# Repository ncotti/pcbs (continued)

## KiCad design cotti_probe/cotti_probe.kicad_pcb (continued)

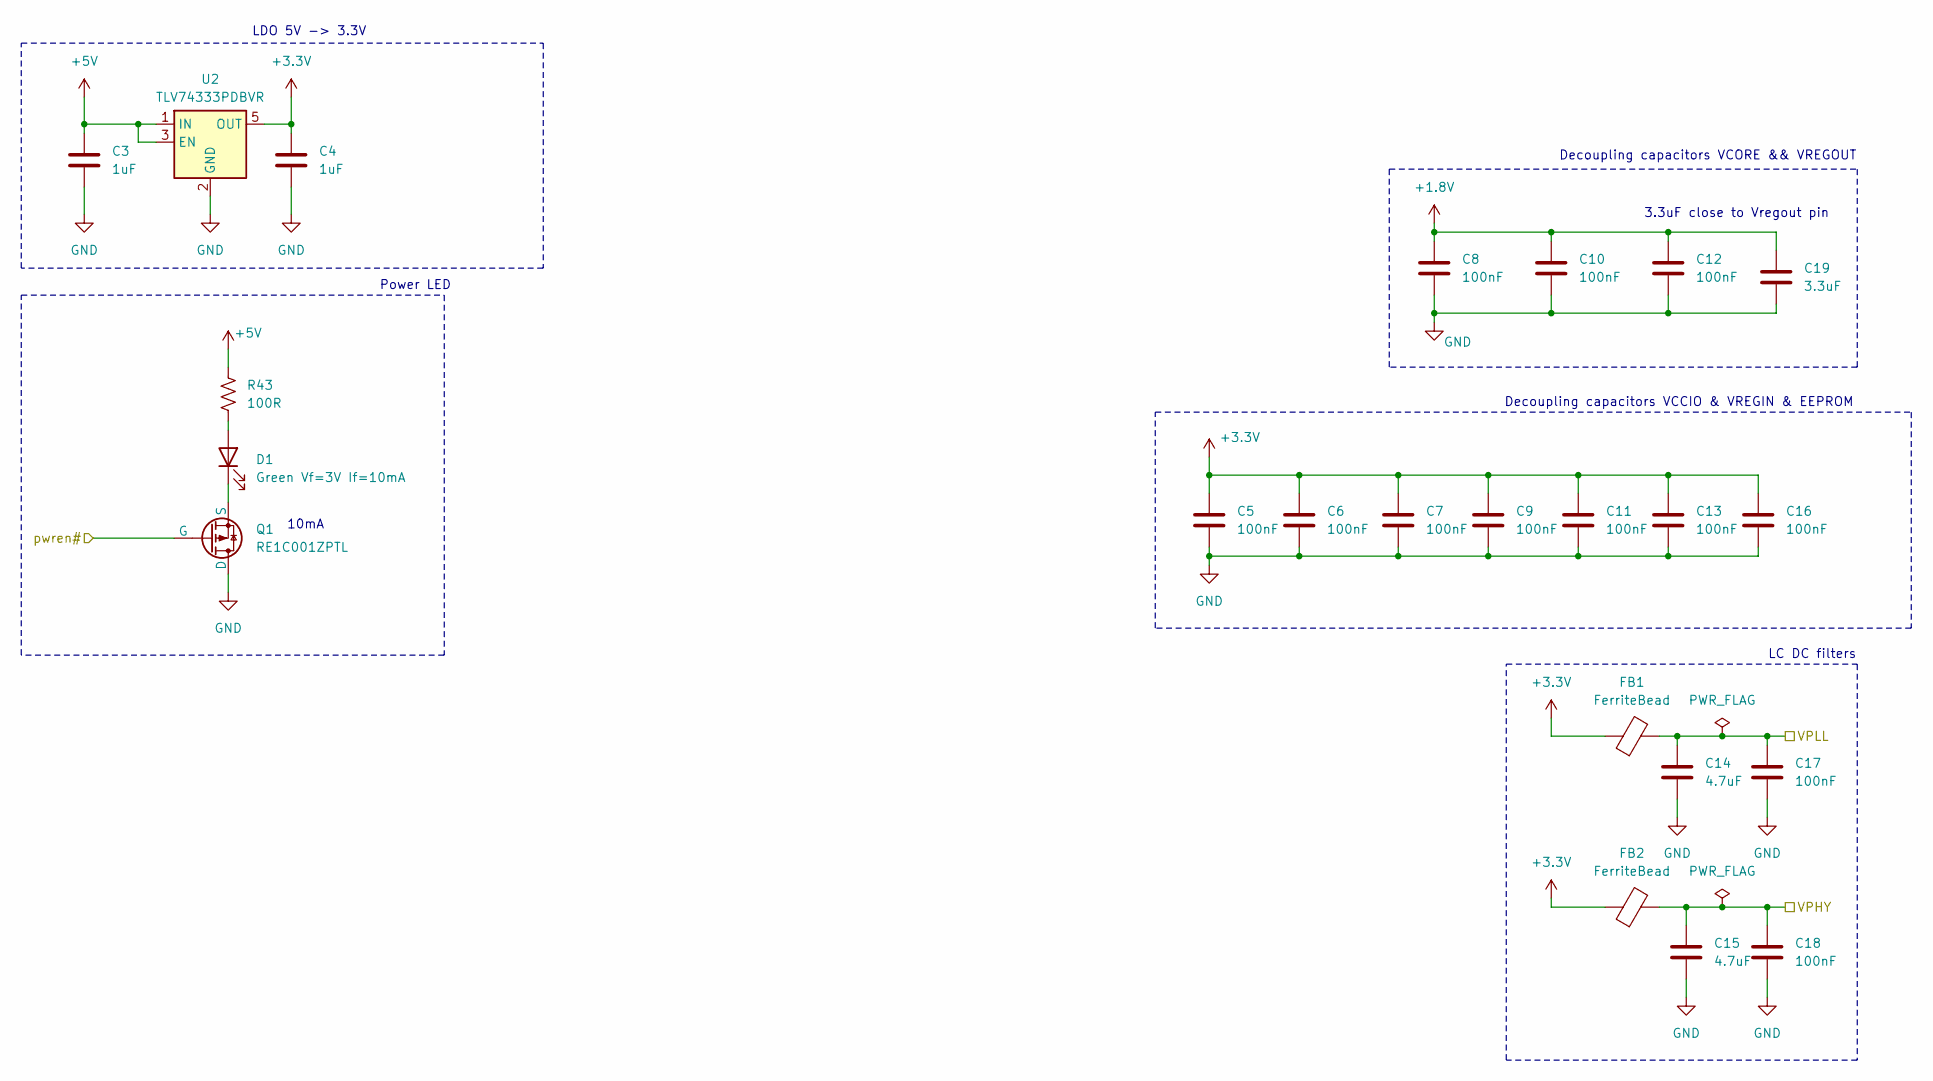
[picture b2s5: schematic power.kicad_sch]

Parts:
C3, C4: 1uF; C_0805_2012Metric_Pad1.18x1.45mm_HandSolder; Mfr. P/N CL21B105KBFNNNE
C5, C6, C7, C8, C9, C10, C11, C12, C13, C16, C17, C18: 100nF; C_0805_2012Metric_Pad1.18x1.45mm_HandSolder; Mfr. P/N CC0805KRX7R9BB104
C14, C15: 4.7uF; C_0805_2012Metric_Pad1.18x1.45mm_HandSolder; Mfr. P/N CL21A475KPFNNNE
C19: 3.3uF; C_0805_2012Metric_Pad1.18x1.45mm_HandSolder; Mfr. P/N CL21A335KPFNNNE
D1: Green Vf=3V If=10mA; LED_0603_1608Metric_Pad1.05x0.95mm_HandSolder; Mfr. P/N B1911PG--20D000514U1930
FB1, FB2: FerriteBead; L_0805_2012Metric_Pad1.05x1.20mm_HandSolder; Mfr. P/N MFBM1V2012-800-R
Q1: RE1C001ZPTL; SOT-416; Mfr. P/N RE1C001ZPTL
R43: 100R; R_0805_2012Metric_Pad1.20x1.40mm_HandSolder; Mfr. P/N RC0805FR-10100RL
U2: TLV74333PDBVR; SOT-23-5; Mfr. P/N TLV74333PDBVR

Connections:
+1.8V: C8.1, C10.1, C12.1, C19.1; also elsewhere on the board
+3.3V: C4.1, C5.1, C6.1, C7.1, C9.1, C11.1, C13.1, C16.1, FB1.1, FB2.1, U2.5 (OUT); also elsewhere on the board
+5V: C3.1, R43.1, U2.1 (IN), U2.3 (EN); also elsewhere on the board
/VPHY: C15.1, C18.1, FB2.2; also elsewhere on the board
/VPLL: C14.1, C17.1, FB1.2; also elsewhere on the board
/pwren#: Q1.1 (G); also elsewhere on the board
GND: C3.2, C4.2, C5.2, C6.2, C7.2, C8.2, C9.2, C10.2, C11.2, C12.2, C13.2, C14.2, C15.2, C16.2, C17.2, C18.2, C19.2, Q1.3 (D), U2.2 (GND); also elsewhere on the board
unnamed: D1.2 (A), R43.2
unnamed: D1.1 (K), Q1.2 (S)

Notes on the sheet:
Power LED
LC DC filters
10mA
LDO 5V -> 3.3V
3.3uF close to Vregout pin
Decoupling capacitors VCORE && VREGOUT
Decoupling capacitors VCCIO & VREGIN & EEPROM

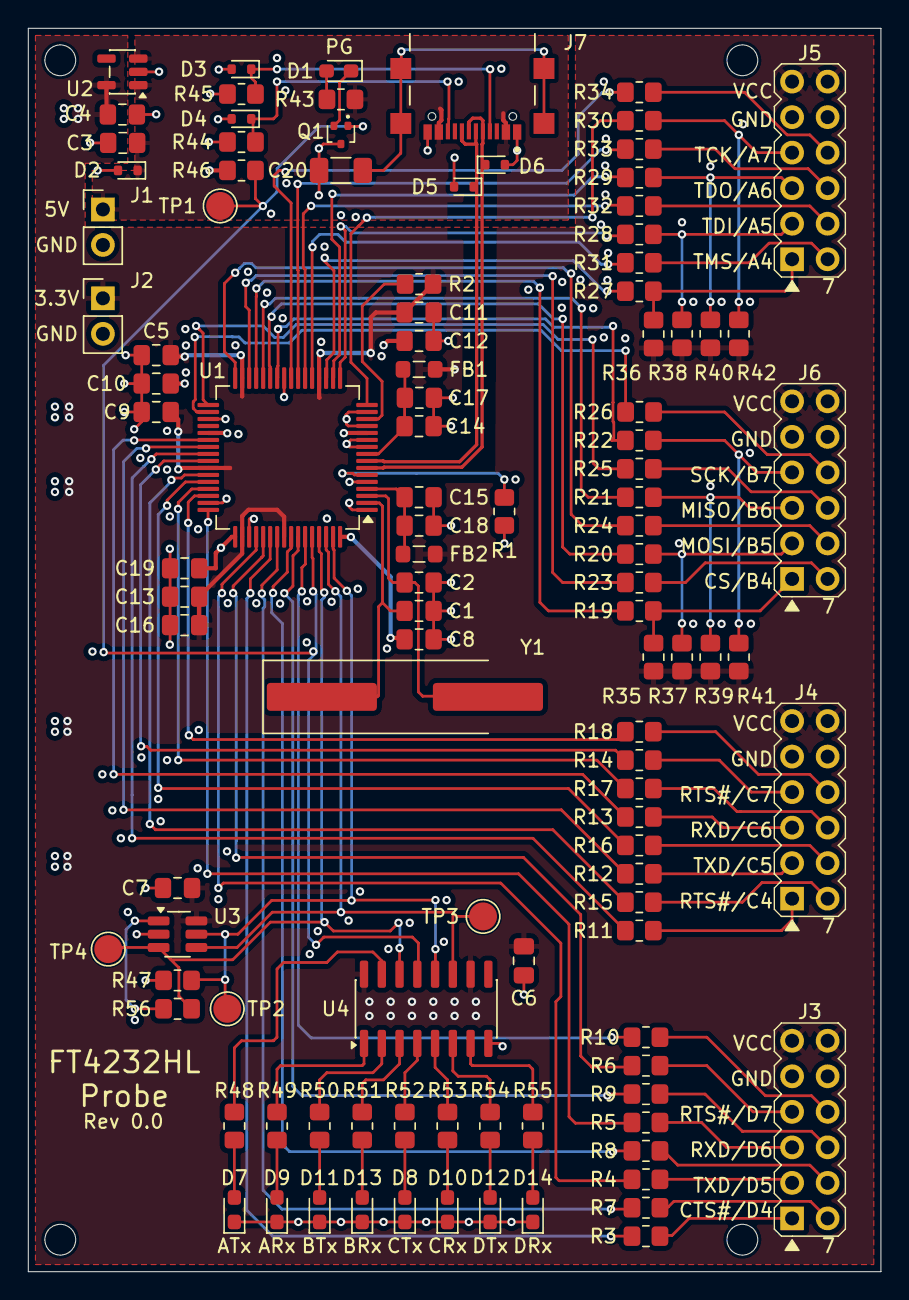
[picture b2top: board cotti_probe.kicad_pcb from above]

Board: 4 copper layers, 61.0 x 88.9 mm, 113 parts (0 on the bottom side), 102 nets.

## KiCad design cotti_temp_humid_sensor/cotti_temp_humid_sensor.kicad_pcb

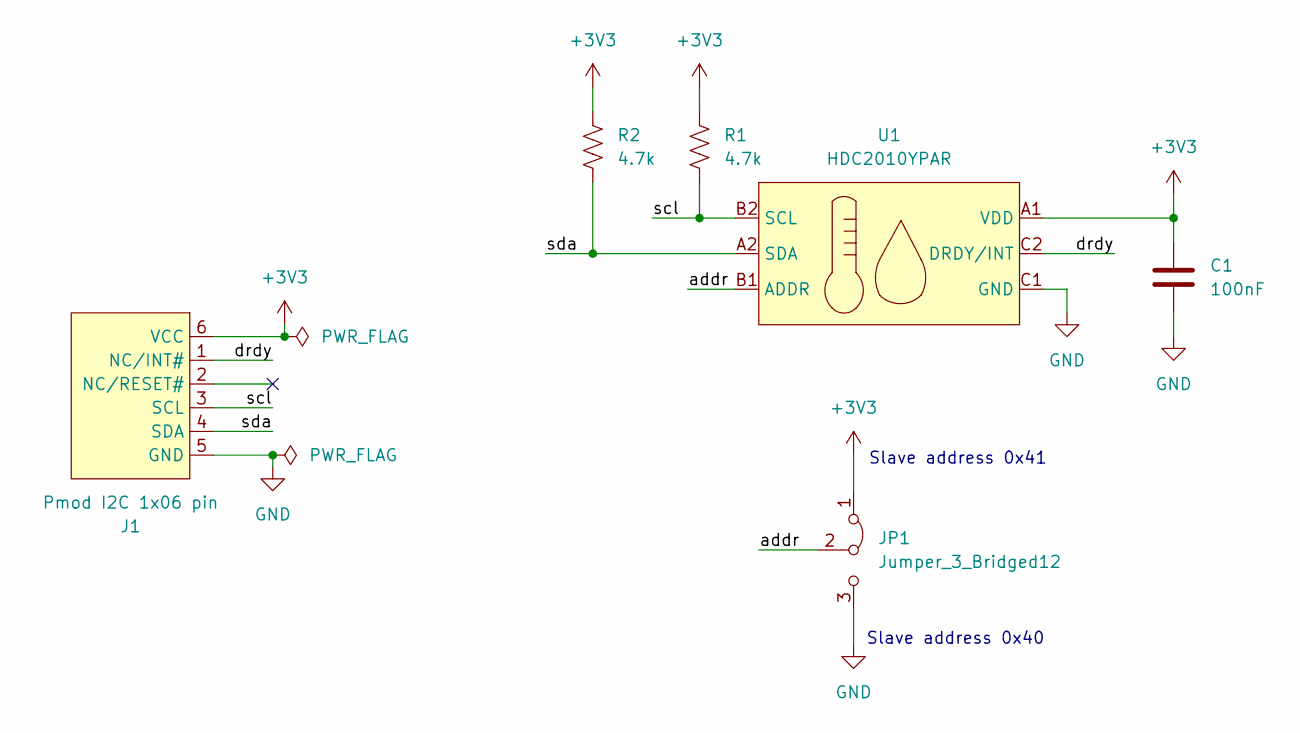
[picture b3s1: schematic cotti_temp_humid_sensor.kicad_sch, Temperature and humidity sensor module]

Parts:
C1: 100nF; C_0805_2012Metric_Pad1.18x1.45mm_HandSolder; Mfr. P/N CC0805KRX7R9BB104
J1: Pmod I2C 1x06 pin; Pmod_1x06_pin; Mfr. P/N PH1RB-06-UA
JP1: Jumper_3_Bridged12; PinHeader_1x03_P2.54mm_Vertical; Mfr. P/N PH1-03-UA
R1, R2: 4.7k; R_0805_2012Metric_Pad1.20x1.40mm_HandSolder; Mfr. P/N RC0805FR-134K7L
U1: HDC2010YPAR; BGA6C100X50P2X3_HDC2010YPAR; Mfr. P/N HDC2010YPAR

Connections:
+3V3: C1.1, J1.6 (VCC), JP1.1 (A), R1.1, R2.1, U1.A1 (VDD)
/addr: JP1.2 (C), U1.B1 (ADDR)
/drdy: J1.1 (NC/INT#), U1.C2 (DRDY/INT)
/scl: J1.3 (SCL), R1.2, U1.B2 (SCL)
/sda: J1.4 (SDA), R2.2, U1.A2 (SDA)
GND: C1.2, J1.5 (GND), JP1.3 (B), U1.C1 (GND)

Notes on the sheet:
Slave address 0x41
Slave address 0x40

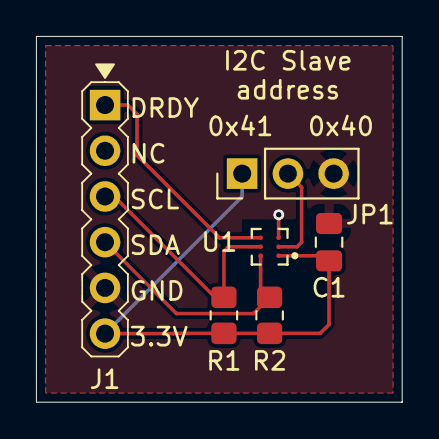
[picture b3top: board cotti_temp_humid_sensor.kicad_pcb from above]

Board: 2 copper layers, 20.3 x 20.3 mm, 6 parts (0 on the bottom side), 6 nets.

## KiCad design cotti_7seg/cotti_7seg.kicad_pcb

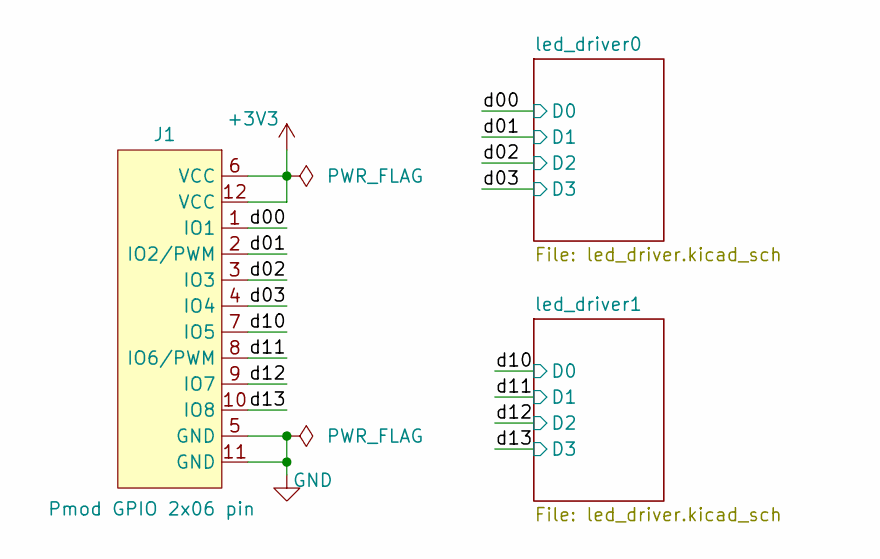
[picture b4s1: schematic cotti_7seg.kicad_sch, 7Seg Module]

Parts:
J1: Pmod GPIO 2x06 pin; Pmod_2x06_pin; Mfr. P/N PH2RA-12-UA

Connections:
/d00: J1.1 (IO1); also elsewhere on the board
/d01: J1.2 (IO2/PWM); also elsewhere on the board
/d02: J1.3 (IO3); also elsewhere on the board
/d03: J1.4 (IO4); also elsewhere on the board
/d10: J1.7 (IO5); also elsewhere on the board
/d11: J1.8 (IO6/PWM); also elsewhere on the board
/d12: J1.9 (IO7); also elsewhere on the board
/d13: J1.10 (IO8); also elsewhere on the board
GND: J1.5 (GND), J1.11 (GND); also elsewhere on the board
VCC: J1.6 (VCC), J1.12 (VCC); also elsewhere on the board

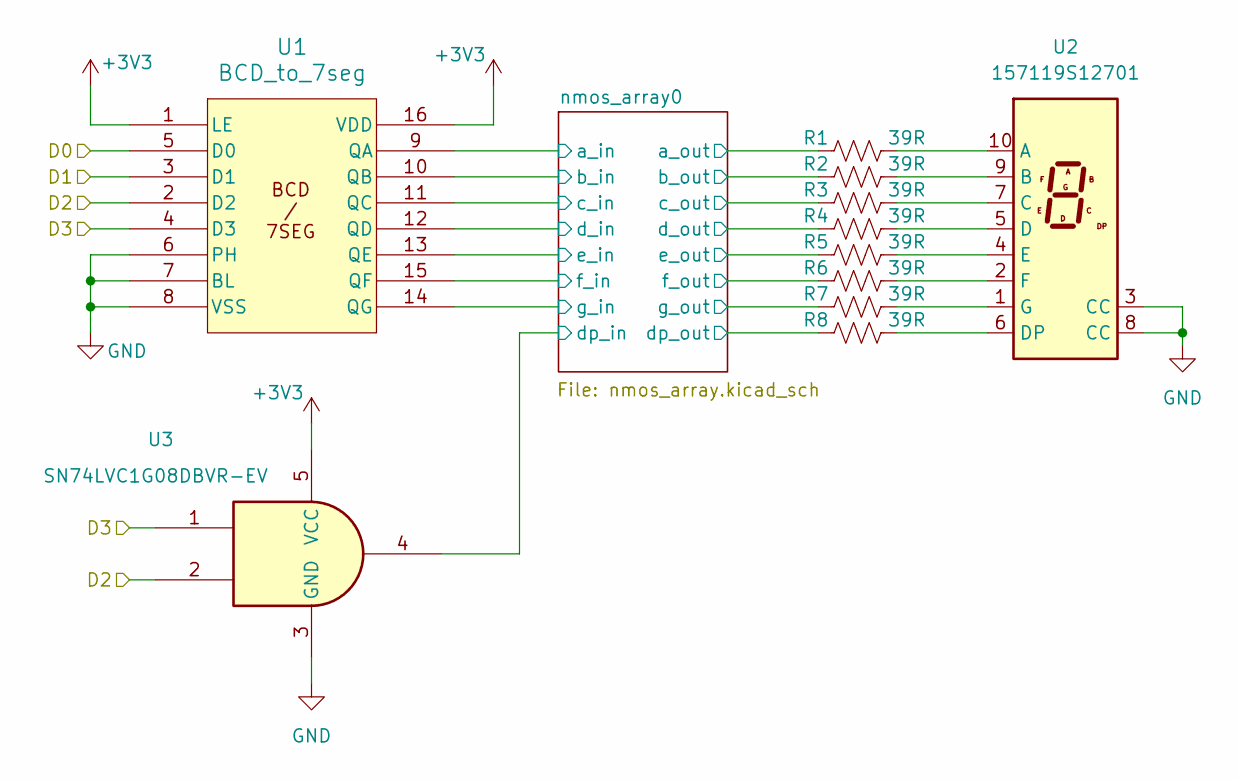
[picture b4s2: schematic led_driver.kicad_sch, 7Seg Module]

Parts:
R1, R2, R3, R4, R5, R6, R7, R8: 39R; R_0805_2012Metric_Pad1.20x1.40mm_HandSolder; Mfr. P/N RC0805FR-0739RL
U1: BCD_to_7seg; SOIC-16_3.9x9.9mm_P1.27mm; Mfr. P/N HEF4543BT,653
U2: 157119S12701; WL-T7DS_0.39INCH; Mfr. P/N 157119S12701
U3: SN74LVC1G08DBVR-EV; SOT-23-5; Mfr. P/N SN74LVC1G08DBVR-EV

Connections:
/d00: U1.5 (D0); also elsewhere on the board
/d01: U1.3 (D1); also elsewhere on the board
/d02: U1.2 (D2), U3.2; also elsewhere on the board
/d03: U1.4 (D3), U3.1; also elsewhere on the board
/led_driver0/nmos_array0/a_in: U1.9 (QA); also elsewhere on the board
/led_driver0/nmos_array0/a_out: R1.1; also elsewhere on the board
/led_driver0/nmos_array0/b_in: U1.10 (QB); also elsewhere on the board
/led_driver0/nmos_array0/b_out: R2.1; also elsewhere on the board
/led_driver0/nmos_array0/c_in: U1.11 (QC); also elsewhere on the board
/led_driver0/nmos_array0/c_out: R3.1; also elsewhere on the board
/led_driver0/nmos_array0/d_in: U1.12 (QD); also elsewhere on the board
/led_driver0/nmos_array0/d_out: R4.1; also elsewhere on the board
/led_driver0/nmos_array0/dp_in: U3.4; also elsewhere on the board
/led_driver0/nmos_array0/dp_out: R8.1; also elsewhere on the board
/led_driver0/nmos_array0/e_in: U1.13 (QE); also elsewhere on the board
/led_driver0/nmos_array0/e_out: R5.1; also elsewhere on the board
/led_driver0/nmos_array0/f_in: U1.15 (QF); also elsewhere on the board
/led_driver0/nmos_array0/f_out: R6.1; also elsewhere on the board
/led_driver0/nmos_array0/g_in: U1.14 (QG); also elsewhere on the board
/led_driver0/nmos_array0/g_out: R7.1; also elsewhere on the board
GND: U1.6 (PH), U1.7 (BL), U1.8 (VSS), U2.3 (CC), U2.8 (CC), U3.3 (GND); also elsewhere on the board
unnamed: R1.2, U2.10 (A)
unnamed: R2.2, U2.9 (B)
unnamed: R3.2, U2.7 (C)
unnamed: R4.2, U2.5 (D)
unnamed: R8.2, U2.6 (DP)
unnamed: R5.2, U2.4 (E)
unnamed: R6.2, U2.2 (F)
unnamed: R7.2, U2.1 (G)
VCC: U1.1 (LE), U1.16 (VDD), U3.5 (VCC); also elsewhere on the board

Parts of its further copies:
R9, R10, R11, R12, R13, R14, R15, R16: 39R; R_0805_2012Metric_Pad1.20x1.40mm_HandSolder; Mfr. P/N RC0805FR-0739RL
U4: BCD_to_7seg; SOIC-16_3.9x9.9mm_P1.27mm; Mfr. P/N HEF4543BT,653
U5: 157119S12701; WL-T7DS_0.39INCH; Mfr. P/N 157119S12701
U6: SN74LVC1G08DBVR-EV; SOT-23-5; Mfr. P/N SN74LVC1G08DBVR-EV

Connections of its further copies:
/d10: U4.5 (D0); also elsewhere on the board
/d11: U4.3 (D1); also elsewhere on the board
/d12: U4.2 (D2), U6.2; also elsewhere on the board
/d13: U4.4 (D3), U6.1; also elsewhere on the board
/led_driver1/nmos_array0/a_in: U4.9 (QA); also elsewhere on the board
/led_driver1/nmos_array0/a_out: R9.1; also elsewhere on the board
/led_driver1/nmos_array0/b_in: U4.10 (QB); also elsewhere on the board
/led_driver1/nmos_array0/b_out: R10.1; also elsewhere on the board
/led_driver1/nmos_array0/c_in: U4.11 (QC); also elsewhere on the board
/led_driver1/nmos_array0/c_out: R11.1; also elsewhere on the board
/led_driver1/nmos_array0/d_in: U4.12 (QD); also elsewhere on the board
/led_driver1/nmos_array0/d_out: R12.1; also elsewhere on the board
/led_driver1/nmos_array0/dp_in: U6.4; also elsewhere on the board
/led_driver1/nmos_array0/dp_out: R16.1; also elsewhere on the board
/led_driver1/nmos_array0/e_in: U4.13 (QE); also elsewhere on the board
/led_driver1/nmos_array0/e_out: R13.1; also elsewhere on the board
/led_driver1/nmos_array0/f_in: U4.15 (QF); also elsewhere on the board
/led_driver1/nmos_array0/f_out: R14.1; also elsewhere on the board
/led_driver1/nmos_array0/g_in: U4.14 (QG); also elsewhere on the board
/led_driver1/nmos_array0/g_out: R15.1; also elsewhere on the board
GND: U4.6 (PH), U4.7 (BL), U4.8 (VSS), U5.3 (CC), U5.8 (CC), U6.3 (GND); also elsewhere on the board
unnamed: R9.2, U5.10 (A)
unnamed: R10.2, U5.9 (B)
unnamed: R11.2, U5.7 (C)
unnamed: R12.2, U5.5 (D)
unnamed: R16.2, U5.6 (DP)
unnamed: R13.2, U5.4 (E)
unnamed: R14.2, U5.2 (F)
unnamed: R15.2, U5.1 (G)
VCC: U4.1 (LE), U4.16 (VDD), U6.5 (VCC); also elsewhere on the board

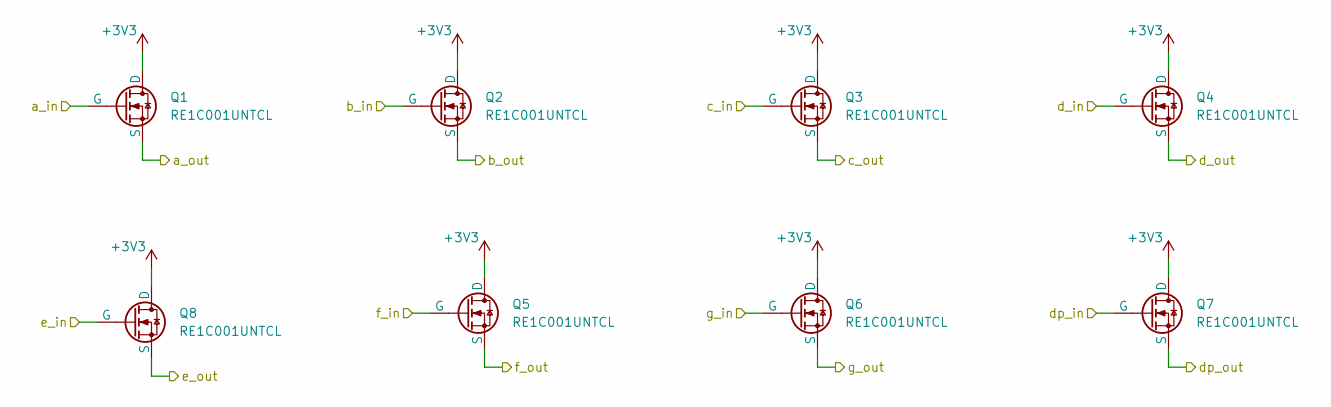
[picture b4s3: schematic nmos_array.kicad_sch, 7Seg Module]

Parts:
Q1, Q2, Q3, Q4, Q5, Q6, Q7, Q8: RE1C001UNTCL; SOT-416; Mfr. P/N RE1C001UNTCL

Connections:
/led_driver0/nmos_array0/a_in: Q1.1 (G); also elsewhere on the board
/led_driver0/nmos_array0/a_out: Q1.2 (S); also elsewhere on the board
/led_driver0/nmos_array0/b_in: Q2.1 (G); also elsewhere on the board
/led_driver0/nmos_array0/b_out: Q2.2 (S); also elsewhere on the board
/led_driver0/nmos_array0/c_in: Q3.1 (G); also elsewhere on the board
/led_driver0/nmos_array0/c_out: Q3.2 (S); also elsewhere on the board
/led_driver0/nmos_array0/d_in: Q4.1 (G); also elsewhere on the board
/led_driver0/nmos_array0/d_out: Q4.2 (S); also elsewhere on the board
/led_driver0/nmos_array0/dp_in: Q7.1 (G); also elsewhere on the board
/led_driver0/nmos_array0/dp_out: Q7.2 (S); also elsewhere on the board
/led_driver0/nmos_array0/e_in: Q8.1 (G); also elsewhere on the board
/led_driver0/nmos_array0/e_out: Q8.2 (S); also elsewhere on the board
/led_driver0/nmos_array0/f_in: Q5.1 (G); also elsewhere on the board
/led_driver0/nmos_array0/f_out: Q5.2 (S); also elsewhere on the board
/led_driver0/nmos_array0/g_in: Q6.1 (G); also elsewhere on the board
/led_driver0/nmos_array0/g_out: Q6.2 (S); also elsewhere on the board
VCC: Q1.3 (D), Q2.3 (D), Q3.3 (D), Q4.3 (D), Q5.3 (D), Q6.3 (D), Q7.3 (D), Q8.3 (D); also elsewhere on the board

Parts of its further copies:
Q9, Q10, Q11, Q12, Q13, Q14, Q15, Q16: RE1C001UNTCL; SOT-416; Mfr. P/N RE1C001UNTCL

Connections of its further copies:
/led_driver1/nmos_array0/a_in: Q9.1 (G); also elsewhere on the board
/led_driver1/nmos_array0/a_out: Q9.2 (S); also elsewhere on the board
/led_driver1/nmos_array0/b_in: Q10.1 (G); also elsewhere on the board
/led_driver1/nmos_array0/b_out: Q10.2 (S); also elsewhere on the board
/led_driver1/nmos_array0/c_in: Q11.1 (G); also elsewhere on the board
/led_driver1/nmos_array0/c_out: Q11.2 (S); also elsewhere on the board
/led_driver1/nmos_array0/d_in: Q12.1 (G); also elsewhere on the board
/led_driver1/nmos_array0/d_out: Q12.2 (S); also elsewhere on the board
/led_driver1/nmos_array0/dp_in: Q15.1 (G); also elsewhere on the board
/led_driver1/nmos_array0/dp_out: Q15.2 (S); also elsewhere on the board
/led_driver1/nmos_array0/e_in: Q16.1 (G); also elsewhere on the board
/led_driver1/nmos_array0/e_out: Q16.2 (S); also elsewhere on the board
/led_driver1/nmos_array0/f_in: Q13.1 (G); also elsewhere on the board
/led_driver1/nmos_array0/f_out: Q13.2 (S); also elsewhere on the board
/led_driver1/nmos_array0/g_in: Q14.1 (G); also elsewhere on the board
/led_driver1/nmos_array0/g_out: Q14.2 (S); also elsewhere on the board
VCC: Q9.3 (D), Q10.3 (D), Q11.3 (D), Q12.3 (D), Q13.3 (D), Q14.3 (D), Q15.3 (D), Q16.3 (D); also elsewhere on the board

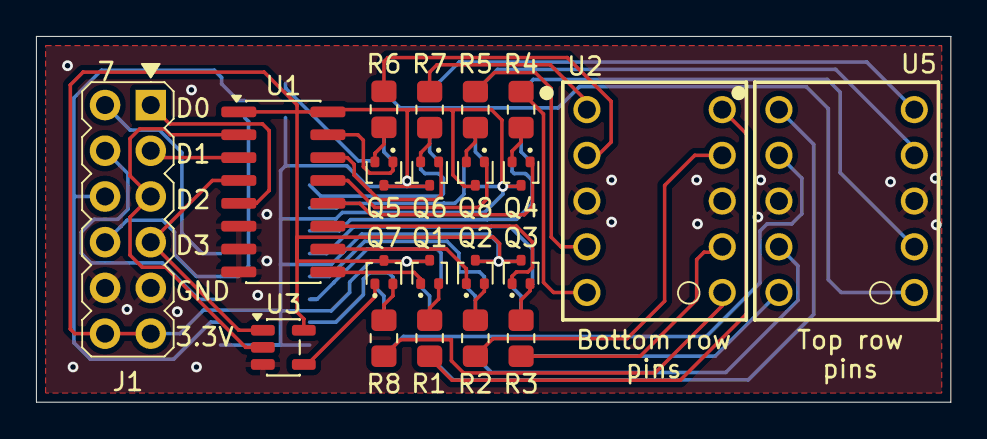
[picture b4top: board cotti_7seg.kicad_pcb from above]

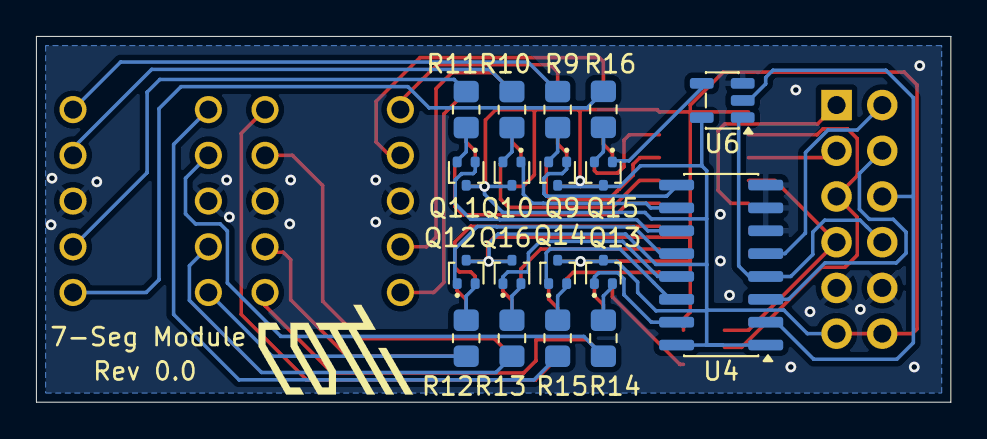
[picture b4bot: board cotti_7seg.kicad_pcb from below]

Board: 2 copper layers, 50.8 x 20.3 mm, 39 parts (18 on the bottom side), 58 nets.

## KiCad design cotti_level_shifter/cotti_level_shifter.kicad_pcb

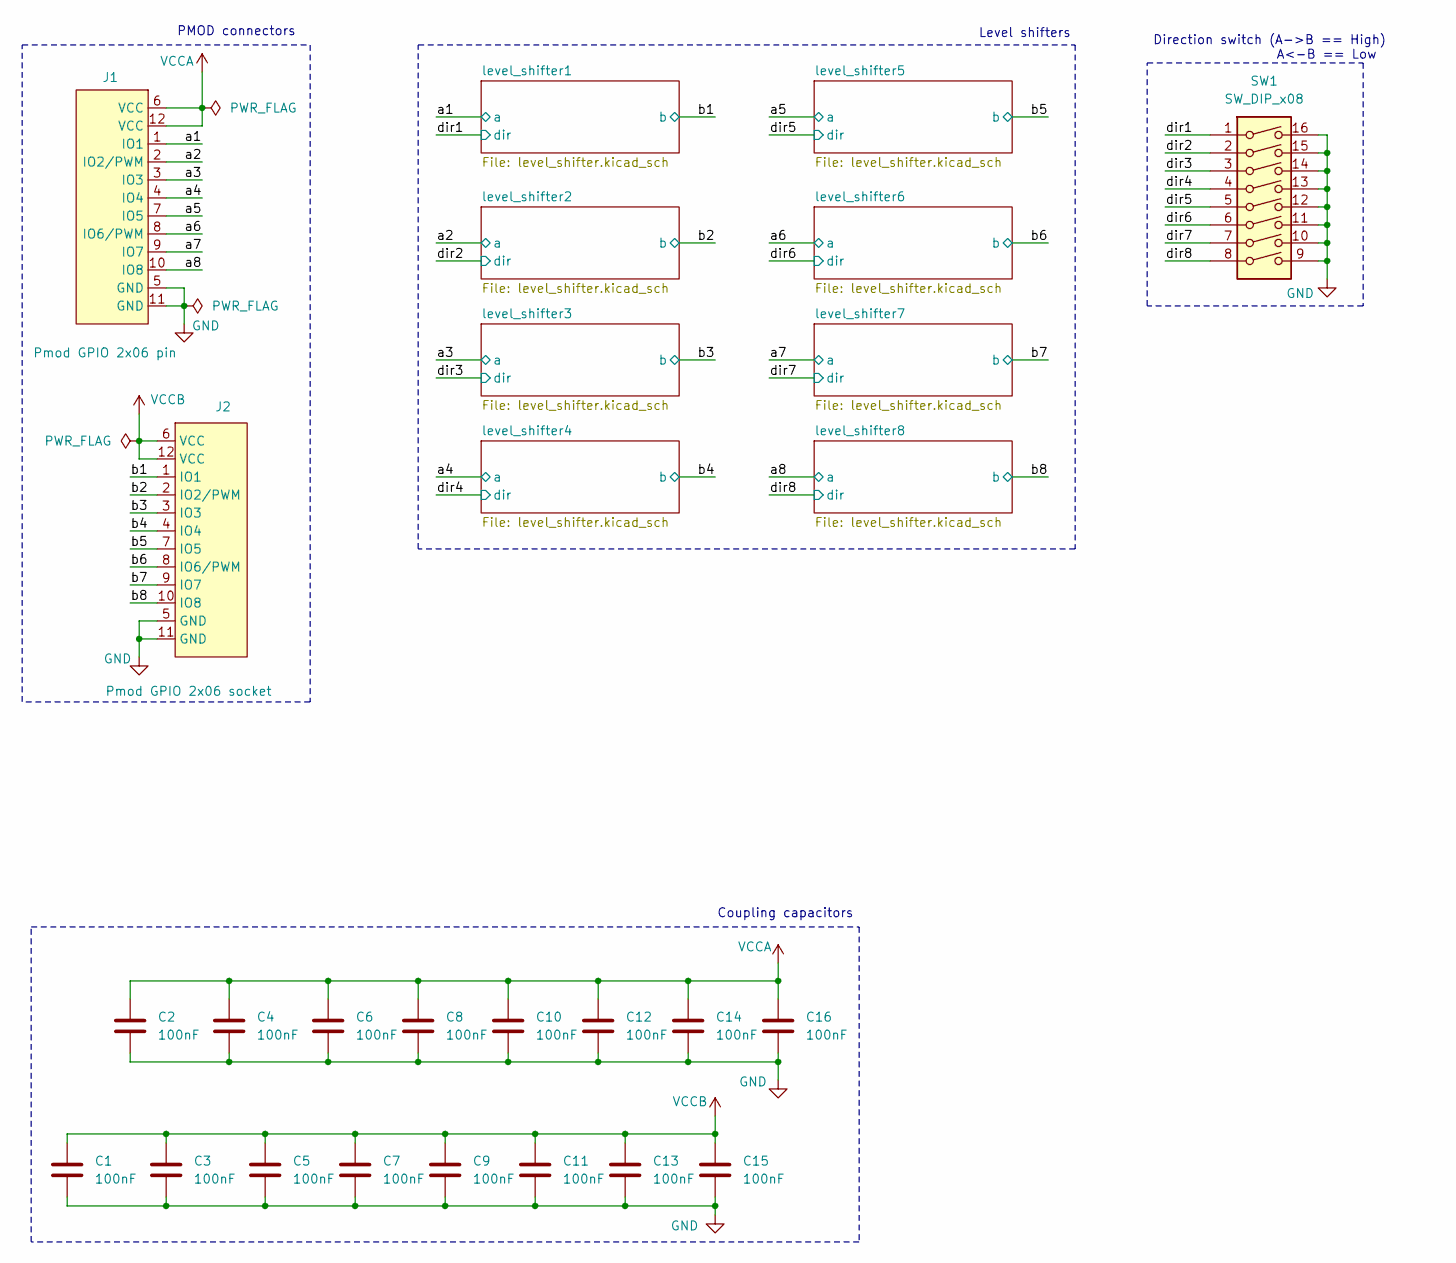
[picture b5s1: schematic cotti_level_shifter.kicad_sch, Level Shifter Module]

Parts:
C1, C2, C3, C4, C5, C6, C7, C8, C9, C10, C11, C12, C13, C14, C15, C16: 100nF; C_0805_2012Metric_Pad1.18x1.45mm_HandSolder; Mfr. P/N CL21B104KBCNNNC; Digikey P/N 1276-1003-1-ND
J1: Pmod GPIO 2x06 pin; Pmod_2x06_pin; Mfr. P/N PH2RA-12-UA
J2: Pmod GPIO 2x06 socket; Pmod_2x06_socket; Mfr. P/N 613012243121
SW1: SW_DIP_x08; SW_DS01C-254-S-08BE; Mfr. P/N DS01C-254-S-08BE

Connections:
/a1: J1.1 (IO1); also elsewhere on the board
/a2: J1.2 (IO2/PWM); also elsewhere on the board
/a3: J1.3 (IO3); also elsewhere on the board
/a4: J1.4 (IO4); also elsewhere on the board
/a5: J1.7 (IO5); also elsewhere on the board
/a6: J1.8 (IO6/PWM); also elsewhere on the board
/a7: J1.9 (IO7); also elsewhere on the board
/a8: J1.10 (IO8); also elsewhere on the board
/b1: J2.1 (IO1); also elsewhere on the board
/b2: J2.2 (IO2/PWM); also elsewhere on the board
/b3: J2.3 (IO3); also elsewhere on the board
/b4: J2.4 (IO4); also elsewhere on the board
/b5: J2.7 (IO5); also elsewhere on the board
/b6: J2.8 (IO6/PWM); also elsewhere on the board
/b7: J2.9 (IO7); also elsewhere on the board
/b8: J2.10 (IO8); also elsewhere on the board
/dir1: SW1.1; also elsewhere on the board
/dir2: SW1.2; also elsewhere on the board
/dir3: SW1.3; also elsewhere on the board
/dir4: SW1.4; also elsewhere on the board
/dir5: SW1.5; also elsewhere on the board
/dir6: SW1.6; also elsewhere on the board
/dir7: SW1.7; also elsewhere on the board
/dir8: SW1.8; also elsewhere on the board
GND: C1.2, C2.2, C3.2, C4.2, C5.2, C6.2, C7.2, C8.2, C9.2, C10.2, C11.2, C12.2, C13.2, C14.2, C15.2, C16.2, J1.5 (GND), J1.11 (GND), J2.5 (GND), J2.11 (GND), SW1.9, SW1.10, SW1.11, SW1.12, SW1.13, SW1.14, SW1.15, SW1.16; also elsewhere on the board
VCCA: C2.1, C4.1, C6.1, C8.1, C10.1, C12.1, C14.1, C16.1, J1.6 (VCC), J1.12 (VCC); also elsewhere on the board
VCCB: C1.1, C3.1, C5.1, C7.1, C9.1, C11.1, C13.1, C15.1, J2.6 (VCC), J2.12 (VCC); also elsewhere on the board

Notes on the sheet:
Level shifters
Coupling capacitors
Direction switch (A->B == High) A<-B == Low
PMOD connectors

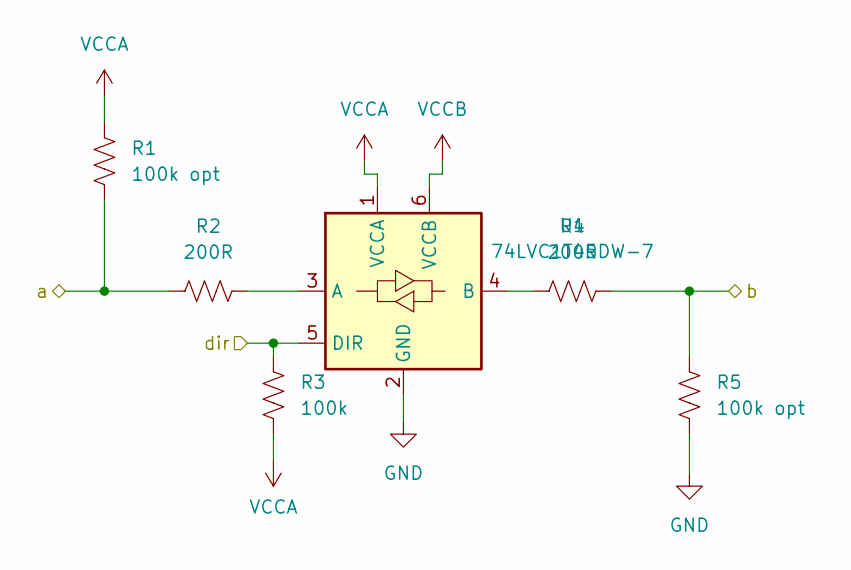
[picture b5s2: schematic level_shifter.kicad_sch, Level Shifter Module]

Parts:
R1, R5: 100k opt; R_0805_2012Metric_Pad1.20x1.40mm_HandSolder; Mfr. P/N AC0805FR-13100KL; Digikey P/N 13-AC0805FR-13100KLCT-ND
R2, R4: 200R; R_0805_2012Metric_Pad1.20x1.40mm_HandSolder; Mfr. P/N RC0805FR-13200RL; Digikey P/N 13-RC0805FR-13200RLCT-ND
R3: 100k; R_0805_2012Metric_Pad1.20x1.40mm_HandSolder; Mfr. P/N AC0805FR-13100KL; Digikey P/N 13-AC0805FR-13100KLCT-ND
U1: 74LVC1T45DW-7; SOT-363_SC-70-6; Mfr. P/N 74LVC1T45DW-7

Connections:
/a1: R1.2, R2.1; also elsewhere on the board
/b1: R4.2, R5.1; also elsewhere on the board
/dir1: R3.1, U1.5 (DIR); also elsewhere on the board
GND: R5.2, U1.2 (GND); also elsewhere on the board
unnamed: R2.2, U1.3 (A)
unnamed: R4.1, U1.4 (B)
VCCA: R1.1, R3.2, U1.1 (VCCA); also elsewhere on the board
VCCB: U1.6 (VCCB); also elsewhere on the board

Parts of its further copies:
R6, R10, R11, R15, R16, R20, R21, R25, R26, R30, R31, R35, R36, R40: 100k opt; R_0805_2012Metric_Pad1.20x1.40mm_HandSolder; Mfr. P/N AC0805FR-13100KL; Digikey P/N 13-AC0805FR-13100KLCT-ND
R7, R9, R12, R14, R17, R19, R22, R24, R27, R29, R32, R34, R37, R39: 200R; R_0805_2012Metric_Pad1.20x1.40mm_HandSolder; Mfr. P/N RC0805FR-13200RL; Digikey P/N 13-RC0805FR-13200RLCT-ND
R8, R13, R18, R23, R28, R33, R38: 100k; R_0805_2012Metric_Pad1.20x1.40mm_HandSolder; Mfr. P/N AC0805FR-13100KL; Digikey P/N 13-AC0805FR-13100KLCT-ND
U2, U3, U4, U5, U6, U7, U8: 74LVC1T45DW-7; SOT-363_SC-70-6; Mfr. P/N 74LVC1T45DW-7

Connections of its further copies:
/a2: R6.2, R7.1; also elsewhere on the board
/a3: R11.2, R12.1; also elsewhere on the board
/a4: R16.2, R17.1; also elsewhere on the board
/a5: R21.2, R22.1; also elsewhere on the board
/a6: R26.2, R27.1; also elsewhere on the board
/a7: R31.2, R32.1; also elsewhere on the board
/a8: R36.2, R37.1; also elsewhere on the board
/b2: R9.2, R10.1; also elsewhere on the board
/b3: R14.2, R15.1; also elsewhere on the board
/b4: R19.2, R20.1; also elsewhere on the board
/b5: R24.2, R25.1; also elsewhere on the board
/b6: R29.2, R30.1; also elsewhere on the board
/b7: R34.2, R35.1; also elsewhere on the board
/b8: R39.2, R40.1; also elsewhere on the board
/dir2: R8.1, U2.5 (DIR); also elsewhere on the board
/dir3: R13.1, U3.5 (DIR); also elsewhere on the board
/dir4: R18.1, U4.5 (DIR); also elsewhere on the board
/dir5: R23.1, U5.5 (DIR); also elsewhere on the board
/dir6: R28.1, U6.5 (DIR); also elsewhere on the board
/dir7: R33.1, U7.5 (DIR); also elsewhere on the board
/dir8: R38.1, U8.5 (DIR); also elsewhere on the board
GND: R10.2, R15.2, R20.2, R25.2, R30.2, R35.2, R40.2, U2.2 (GND), U3.2 (GND), U4.2 (GND), U5.2 (GND), U6.2 (GND), U7.2 (GND), U8.2 (GND); also elsewhere on the board
unnamed: R7.2, U2.3 (A)
unnamed: R9.1, U2.4 (B)
unnamed: R12.2, U3.3 (A)
unnamed: R14.1, U3.4 (B)
unnamed: R17.2, U4.3 (A)
unnamed: R19.1, U4.4 (B)
unnamed: R22.2, U5.3 (A)
unnamed: R24.1, U5.4 (B)
unnamed: R27.2, U6.3 (A)
unnamed: R29.1, U6.4 (B)
unnamed: R32.2, U7.3 (A)
unnamed: R34.1, U7.4 (B)
unnamed: R37.2, U8.3 (A)
unnamed: R39.1, U8.4 (B)
VCCA: R6.1, R8.2, R11.1, R13.2, R16.1, R18.2, R21.1, R23.2, R26.1, R28.2, R31.1, R33.2, R36.1, R38.2, U2.1 (VCCA), U3.1 (VCCA), U4.1 (VCCA), U5.1 (VCCA), U6.1 (VCCA), U7.1 (VCCA), U8.1 (VCCA); also elsewhere on the board
VCCB: U2.6 (VCCB), U3.6 (VCCB), U4.6 (VCCB), U5.6 (VCCB), U6.6 (VCCB), U7.6 (VCCB), U8.6 (VCCB); also elsewhere on the board

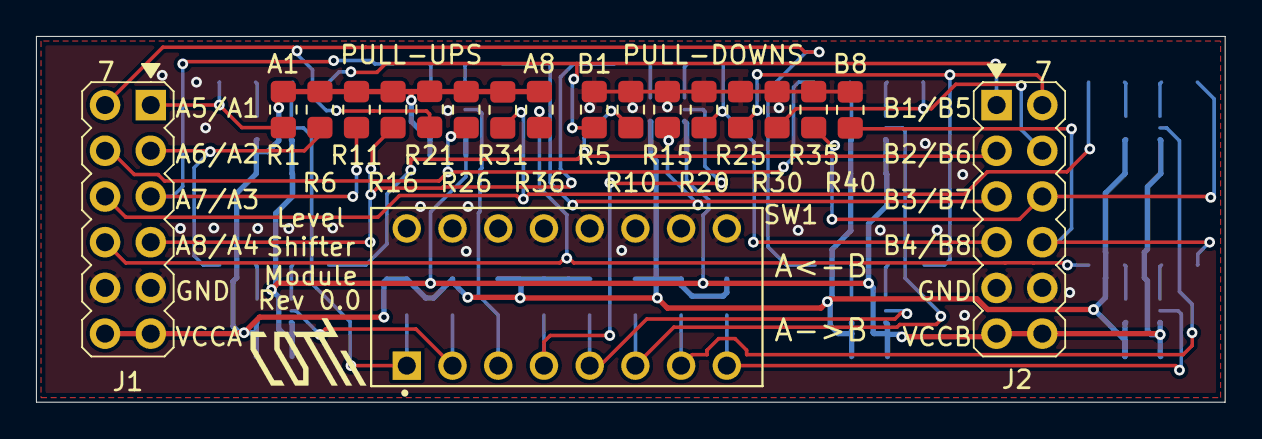
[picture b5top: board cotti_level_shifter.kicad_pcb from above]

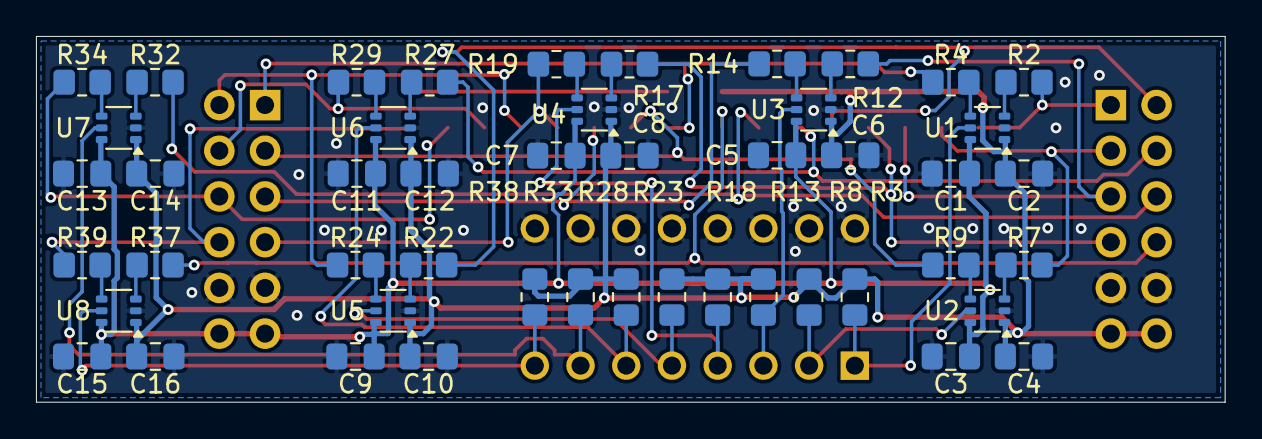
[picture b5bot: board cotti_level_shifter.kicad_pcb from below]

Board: 2 copper layers, 66.0 x 20.3 mm, 67 parts (48 on the bottom side), 43 nets.

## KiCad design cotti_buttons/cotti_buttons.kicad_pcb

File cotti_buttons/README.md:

# Bibliography

tau = RC

https://www.ti.com/lit/ab/scea094/scea094.pdf?ts=1766034050027&ref_url=https%253A%252F%252Fduckduckgo.com%252F

Add a diode, so that the time constant is "R1 * C" while charging, and "R2 * C" while discharging.

There should always be a schmmit trigger. Since the voltage is exponential, the values within a logic "low" and a logic "high" are undefined when read by the GPIO pin.
Add the schmiit trigger to avoid intermmidiate values, thanks to its hysteresis.

https://my.eng.utah.edu/~cs5780/debouncing.pdf

JTAG interfaces

https://www2.lauterbach.com/pdf/app_arm_jtag.pdf

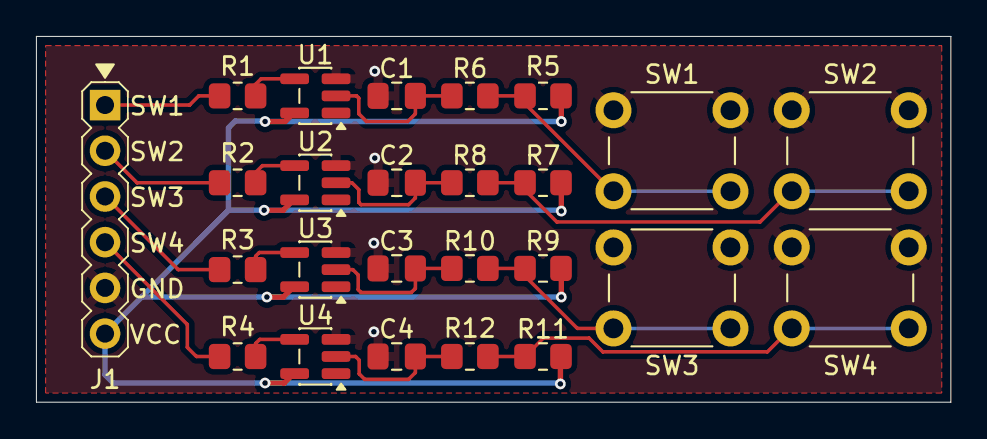
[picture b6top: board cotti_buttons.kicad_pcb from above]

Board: 2 copper layers, 50.8 x 20.3 mm, 25 parts (0 on the bottom side), 18 nets.

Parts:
C1, C2, C3, C4: 0.47uF; C_0805_2012Metric_Pad1.18x1.45mm_HandSolder
J1: Pmod GPIO 1x06 pin; Pmod_1x06_pin
R1, R2, R3, R4: 200R; R_0805_2012Metric_Pad1.20x1.40mm_HandSolder
R5, R6, R7, R8, R9, R10, R11, R12: 10k; R_0805_2012Metric_Pad1.20x1.40mm_HandSolder
SW1, SW2, SW3, SW4: SW_Push_Dual; SW_PUSH_6mm_H5mm
U1, U2, U3, U4: MC74VHC1GT14DBVT1G; SC-74A-5_1.55x2.9mm_P0.95mm

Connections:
/io1: R1.2, U1.4
/io2: R2.2, U2.4
/io3: R3.2, U3.4
/io4: R4.2, U4.4
GND: C1.2, C2.2, C3.2, C4.2, J1.5 (GND), SW1.1, SW2.1, SW3.1, SW4.1, U1.3 (GND), U2.3 (GND), U3.3 (GND), U4.3 (GND)
unnamed: C1.1, R6.2, U1.2
unnamed: C2.1, R8.2, U2.2
unnamed: C3.1, R10.2, U3.2
unnamed: C4.1, R12.2, U4.2
unnamed: J1.1 (IO1), R1.1
unnamed: J1.2 (IO2/PWM), R2.1
unnamed: J1.3 (IO3), R3.1
unnamed: J1.4 (IO4), R4.1
unnamed: R5.2, R6.1, SW1.2
unnamed: R7.2, R8.1, SW2.2
unnamed: R9.2, R10.1, SW3.2
unnamed: R11.2, R12.1, SW4.2
VCC: J1.6 (VCC), R5.1, R7.1, R9.1, R11.1, U1.5 (VCC), U2.5 (VCC), U3.5 (VCC), U4.5 (VCC)
